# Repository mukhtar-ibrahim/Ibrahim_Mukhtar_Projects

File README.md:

# Ibrahim_Mukhtar_Projects
A collection of my projects on ML, Control Engineering and PCB design

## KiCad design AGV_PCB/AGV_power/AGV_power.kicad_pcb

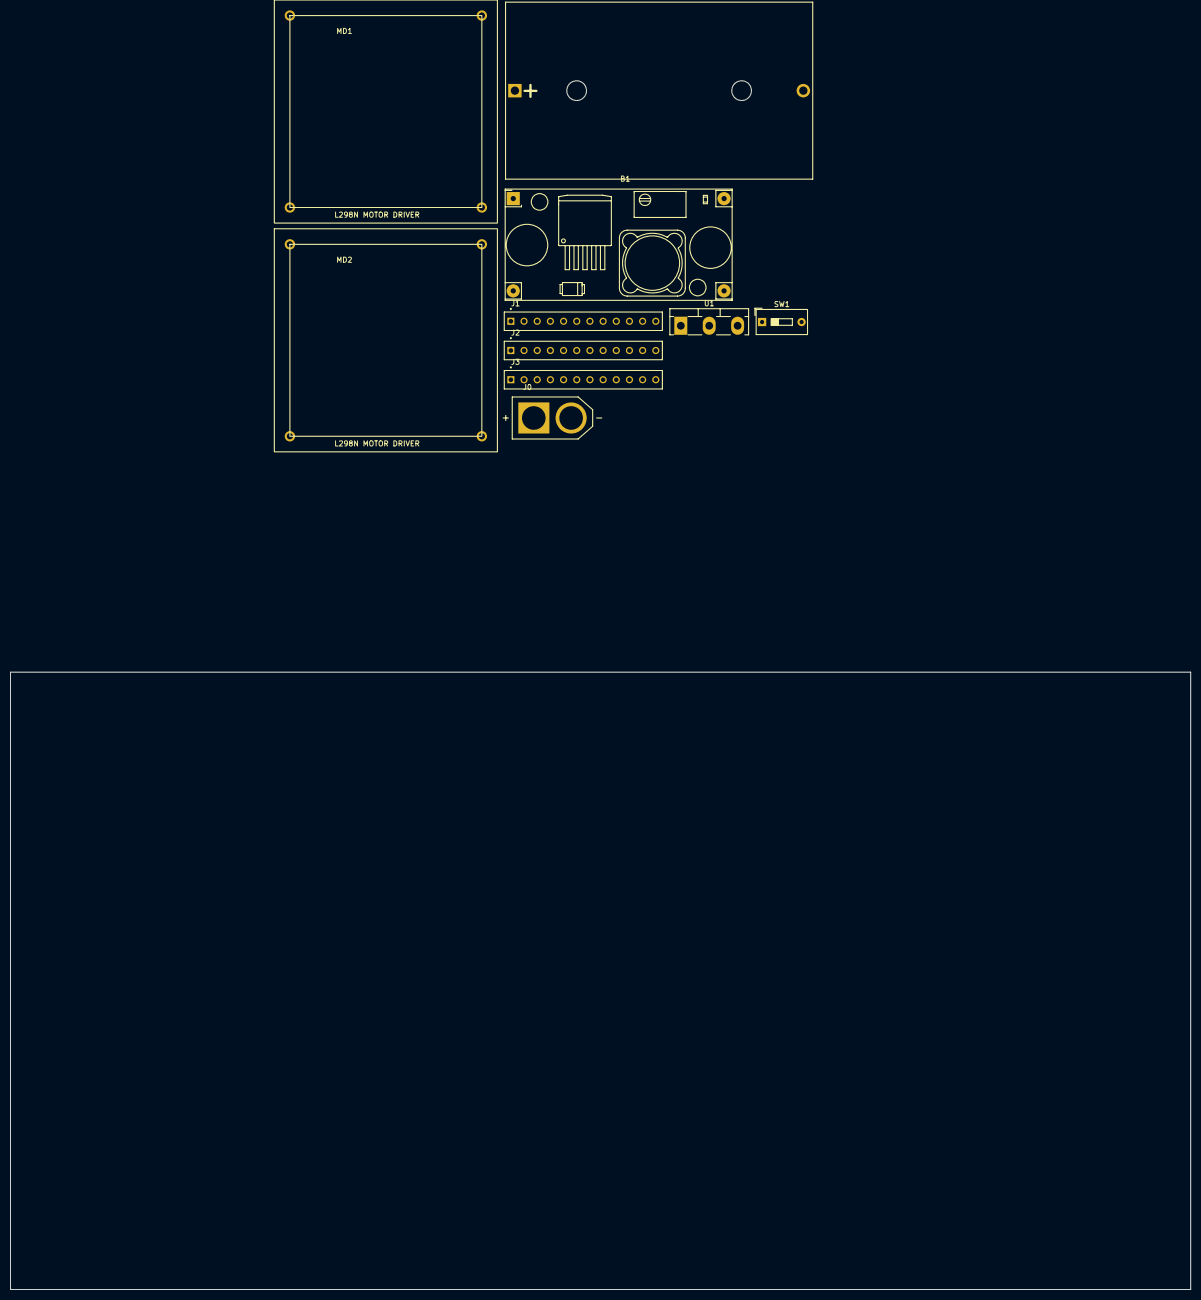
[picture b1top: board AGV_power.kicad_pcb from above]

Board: 2 copper layers, 227.5 x 119.0 mm, 10 parts (0 on the bottom side), 4 nets, no tracks yet.

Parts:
B1: YAAJ_DCDC_StepDown_LM2596
BT1: 12V; BatteryHolder_Bulgin_BX0036_1xC
J0: XT60-M; AMASS_XT60-M
J1, J2, J3: Conn_01x12_Pin; TE_6-534237-0
MD1, MD2: motor_driver_nex6
SW1: SW_SPST; SW_DIP_SPSTx01_Slide_9.78x4.72mm_W7.62mm_P2.54mm
U1: LM1117T-3.3; TO-218-3_Vertical

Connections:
+3.3V: J1.1, J1.2, J1.3, J1.4, J1.5, J1.6, J1.7, J1.8, J1.9, J1.10, J1.11, J1.12, U1.2 (VO)
+12V: B1.1 (VIN+), BT1.1 (+), J0.P (POS), SW1.1 (A), SW1.2 (B)
unnamed: B1.2 (VIN-), BT1.2 (-), J0.N (NEG), J3.1, J3.2, J3.3, J3.4, J3.5, J3.6, J3.7, J3.8, J3.9, J3.10, J3.11, J3.12
unnamed: B1.3 (VOUT+), J2.1, J2.2, J2.3, J2.4, J2.5, J2.6, J2.7, J2.8, J2.9, J2.10, J2.11, J2.12

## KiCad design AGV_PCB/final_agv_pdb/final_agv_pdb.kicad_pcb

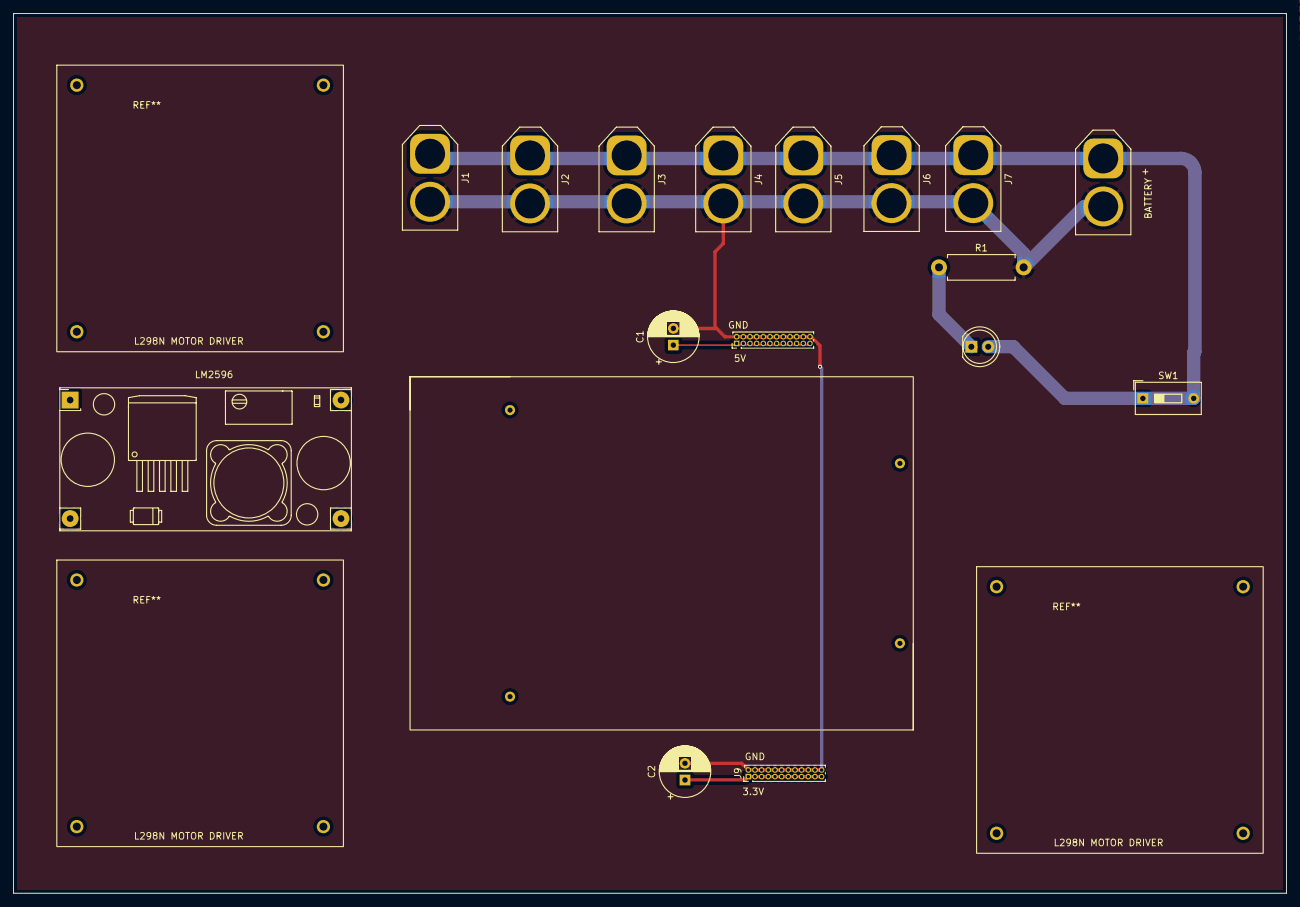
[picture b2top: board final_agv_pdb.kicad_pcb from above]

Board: 2 copper layers, 191.0 x 132.0 mm, 16 parts (0 on the bottom side), 5 nets.

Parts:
5V: Conn_02x12_Odd_Even; PinHeader_2x12_P1.00mm_Vertical
BATTERY: Battery_Cell; AMASS_XT60-F_1x02_P7.20mm_Vertical
C1, C2: C_Polarized_Small; CP_Radial_D7.5mm_P2.50mm
D1: LED; LED_D5.0mm
J1, J2, J3, J4, J5, J6, J7: Screw_Terminal_01x02; AMASS_XT60-M_1x02_P7.20mm_Vertical
J9: Conn_02x12_Odd_Even; PinHeader_2x12_P1.00mm_Vertical
LM2596: YAAJ_DCDC_StepDown_LM2596
R1: R; R_Axial_DIN0411_L9.9mm_D3.6mm_P12.70mm_Horizontal
SW1: SW_SPST; SW_DIP_SPSTx01_Slide_9.78x4.72mm_W7.62mm_P2.54mm

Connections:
/3.3V: C2.1, J9.1, J9.3, J9.5, J9.7, J9.9, J9.11, J9.13, J9.15, J9.17, J9.19, J9.21, J9.23
/5V: 5V.1, 5V.3, 5V.5, 5V.7, 5V.9, 5V.11, 5V.13, 5V.15, 5V.17, 5V.19, 5V.21, 5V.23, C1.1
/GND: 5V.2, 5V.4, 5V.6, 5V.8, 5V.10, 5V.12, 5V.14, 5V.16, 5V.18, 5V.20, 5V.22, 5V.24, BATTERY.2 (-), C1.2, C2.2, J1.2, J2.2, J3.2, J4.2, J5.2, J6.2, J7.2, J9.2, J9.4, J9.6, J9.8, J9.10, J9.12, J9.14, J9.16, J9.18, J9.20, J9.22, J9.24, R1.2
/L: D1.1 (K), R1.1
/VCC: BATTERY.1 (+), D1.2 (A), J1.1, J2.1, J3.1, J4.1, J5.1, J6.1, J7.1, SW1.1 (A), SW1.2 (B)

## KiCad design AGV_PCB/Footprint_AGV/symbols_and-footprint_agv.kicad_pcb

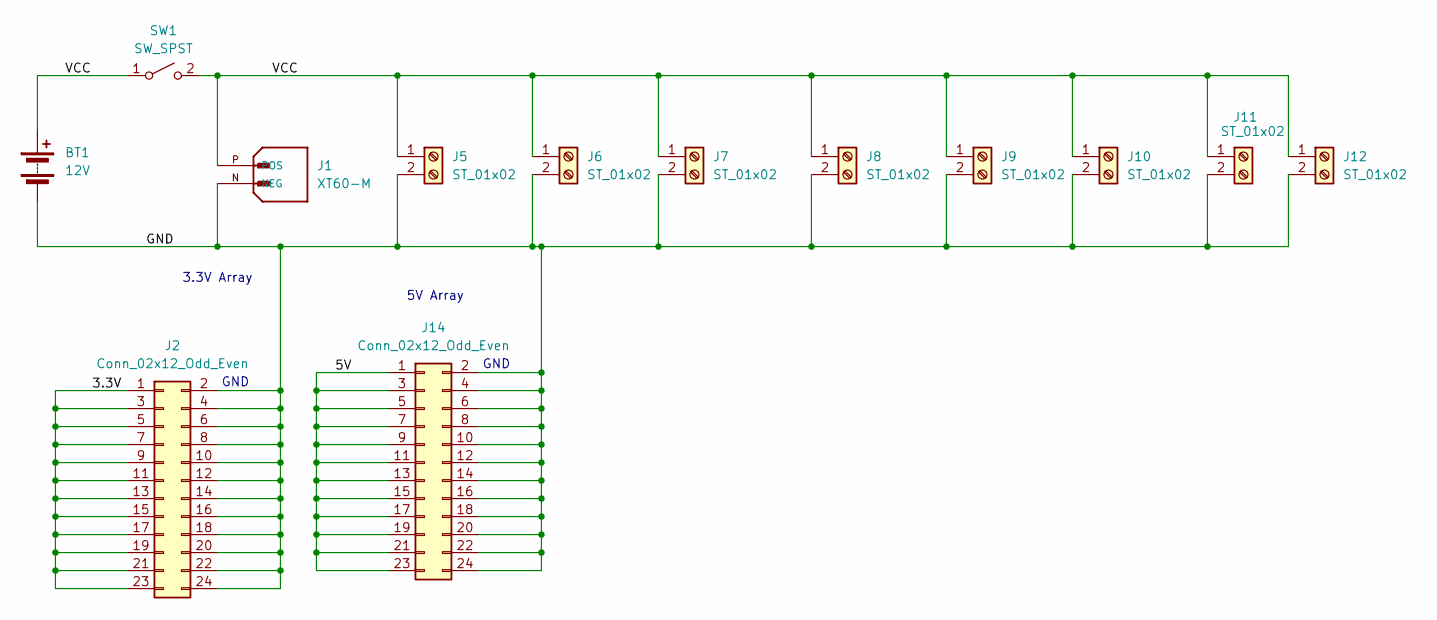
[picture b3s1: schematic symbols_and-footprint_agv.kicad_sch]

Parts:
BT1: 12V; BatteryHolder_Bulgin_BX0036_1xC
J1: XT60-M; AMASS_XT60-M_1x02_P7.20mm_Vertical; PARTREV V1.2
J2, J14: Conn_02x12_Odd_Even; PinHeader_2x12_P1.27mm_Vertical
J5: ST_01x02; AMASS_XT60-M_1x02_P7.20mm_Vertical
J6, J7, J8, J9, J10, J11, J12: ST_01x02; AMASS_XT60-F_1x02_P7.20mm_Vertical
SW1: SW_SPST; SW_DIP_SPSTx01_Slide_6.7x4.1mm_W7.62mm_P2.54mm_LowProfile

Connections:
/3.3V: J2.1, J2.3, J2.5, J2.7, J2.9, J2.11, J2.13, J2.15, J2.17, J2.19, J2.21, J2.23
/5V: J14.1, J14.3, J14.5, J14.7, J14.9, J14.11, J14.13, J14.15, J14.17, J14.19, J14.21, J14.23
/GND: BT1.2 (-), J1.N (NEG), J2.2, J2.4, J2.6, J2.8, J2.10, J2.12, J2.14, J2.16, J2.18, J2.20, J2.22, J2.24, J5.2, J6.2, J7.2, J8.2, J9.2, J10.2, J11.2, J12.2, J14.2, J14.4, J14.6, J14.8, J14.10, J14.12, J14.14, J14.16, J14.18, J14.20, J14.22, J14.24
/VCC: BT1.1 (+), J1.P (POS), J5.1, J6.1, J7.1, J8.1, J9.1, J10.1, J11.1, J12.1, SW1.1 (A), SW1.2 (B)

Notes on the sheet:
3.3V Array
5V Array
GND

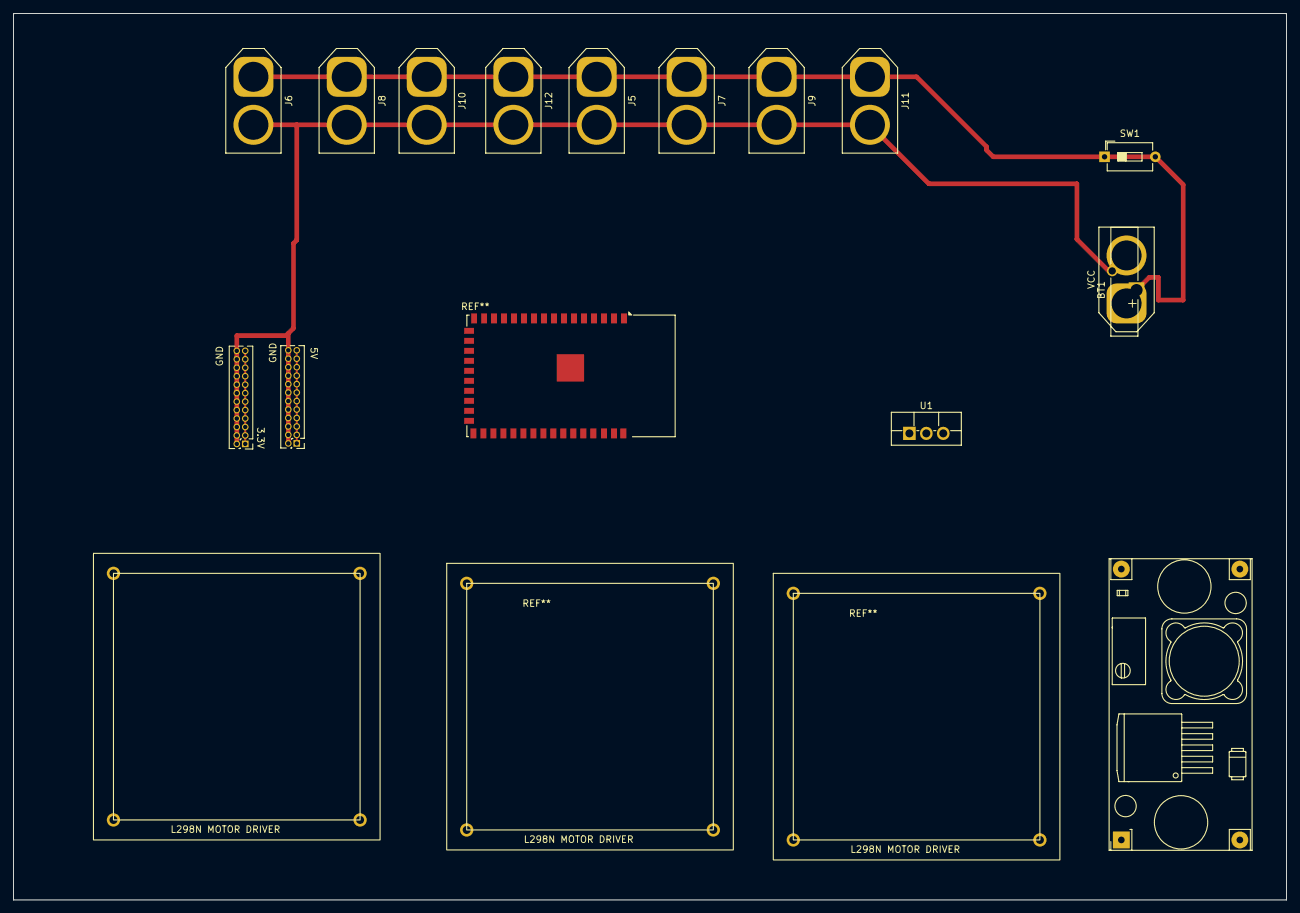
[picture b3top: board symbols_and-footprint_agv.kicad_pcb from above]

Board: 2 copper layers, 191.0 x 133.0 mm, 14 parts (0 on the bottom side), 4 nets.

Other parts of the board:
U1: LM1117T-3.3; TO-220F-3_Vertical
VCC: XT60-M; AMASS_XT60-F_1x02_P7.20mm_Vertical

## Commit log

2025-09-02 Updated air_quality_prediction.ipynb
2025-09-02 first commit - committing all files to the repository
2025-09-02 Added new project: [project-name]
2025-09-02 Updated projects
